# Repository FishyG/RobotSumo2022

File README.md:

# RobotSumo2022

Hello test :)

Hi test. I'm funny.

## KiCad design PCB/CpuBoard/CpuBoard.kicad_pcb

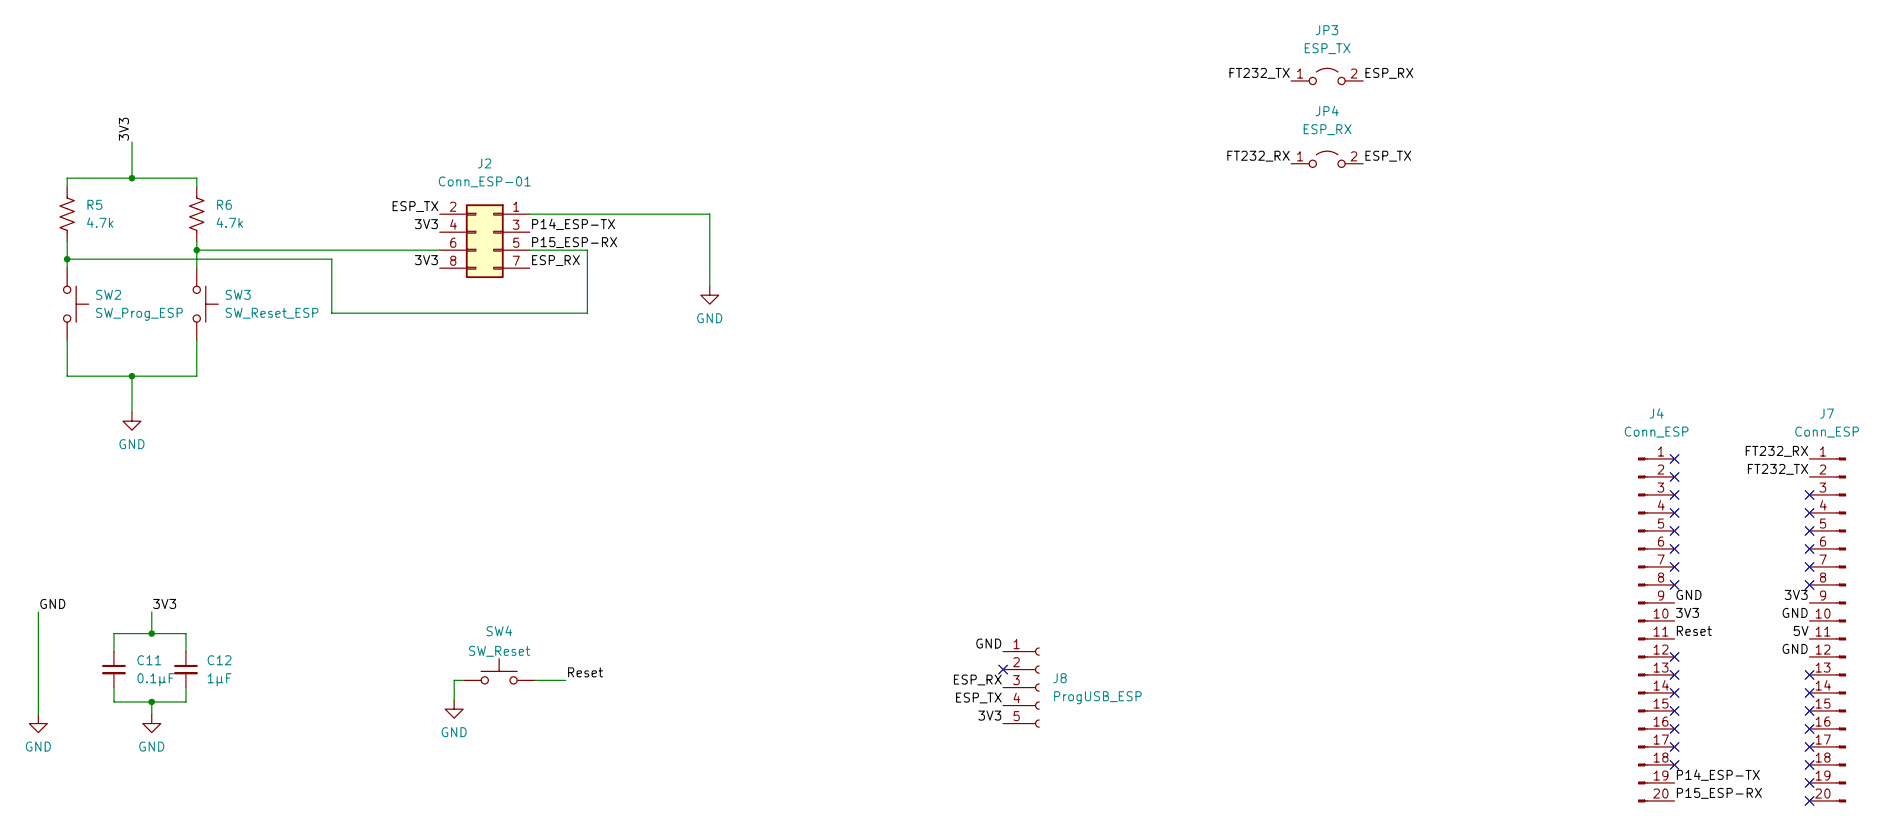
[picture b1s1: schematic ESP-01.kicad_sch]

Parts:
C11: 0.1µF; C_0805_2012Metric_Pad1.18x1.45mm_HandSolder
C12: 1µF; C_0805_2012Metric_Pad1.18x1.45mm_HandSolder
J2: Conn_ESP-01; PinSocket_2x04_P2.54mm_Vertical
J4: Conn_ESP; PinSocket_1x20_P2.54mm_Vertical
J7: Conn_ESP; PinHeader_1x20_P2.54mm_Vertical
J8: ProgUSB_ESP; PinSocket_1x05_P2.54mm_Vertical
JP3: ESP_TX; PinHeader_1x02_P2.54mm_Vertical
JP4: ESP_RX; PinHeader_1x02_P2.54mm_Vertical
R5, R6: 4.7k; R_0805_2012Metric_Pad1.20x1.40mm_HandSolder
SW2: SW_Prog_ESP; SW_SPST_CK_RS282G05A3
SW3: SW_Reset_ESP; SW_SPST_CK_RS282G05A3
SW4: SW_Reset; SW_SPST_CK_RS282G05A3

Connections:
/ESP-01/3V3: C11.1, C12.1, J2.4, J2.8, J4.10, J7.9, J8.5, R5.1, R6.1
/ESP-01/5V: J7.11
/ESP-01/ESP_RX: J2.7, J8.3, JP3.2 (B)
/ESP-01/ESP_TX: J2.2, J8.4, JP4.2 (B)
/ESP-01/FT232_RX: J7.1, JP4.1 (A)
/ESP-01/FT232_TX: J7.2, JP3.1 (A)
/ESP-01/P14_ESP-TX: J2.3, J4.19
/ESP-01/P15_ESP-RX: J2.5, J4.20, R5.2, SW2.1
/ESP-01/Reset: J4.11, SW4.2
GND: C11.2, C12.2, J2.1, J4.9, J7.10, J7.12, J8.1, SW2.2, SW3.2, SW4.1; also elsewhere on the board
unnamed: J2.6, R6.2, SW3.1

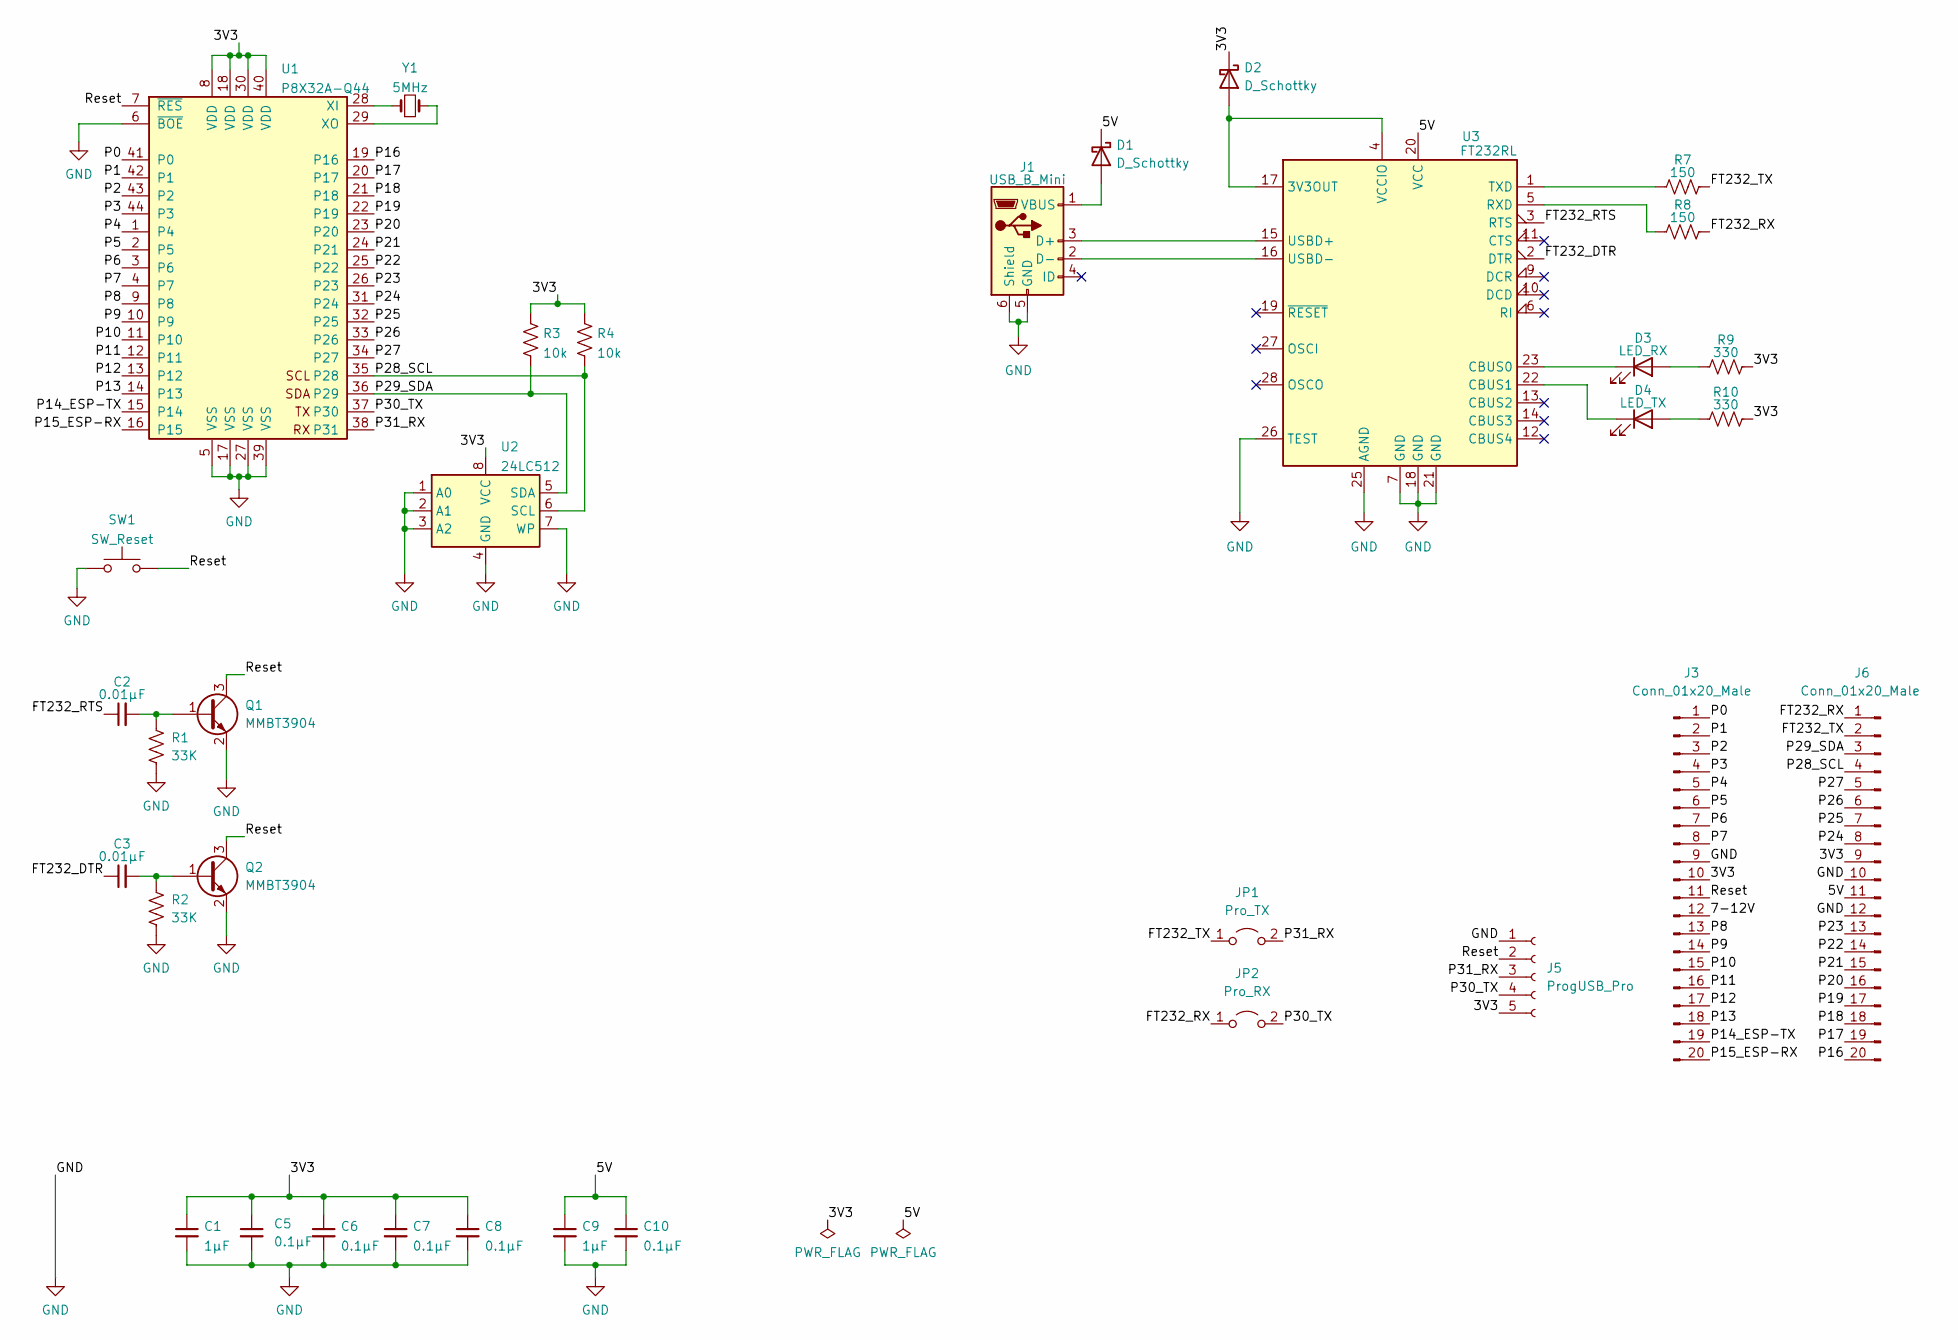
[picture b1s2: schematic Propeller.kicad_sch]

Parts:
C1: 1µF; C_0805_2012Metric_Pad1.18x1.45mm_HandSolder
C2, C3: 0.01µF; C_0805_2012Metric_Pad1.18x1.45mm_HandSolder
C5, C6, C7, C8: 0.1µF; C_0805_2012Metric_Pad1.18x1.45mm_HandSolder
C9: 1µF; C_0603_1608Metric_Pad1.08x0.95mm_HandSolder
C10: 0.1µF; C_0603_1608Metric_Pad1.08x0.95mm_HandSolder
D1, D2: D_Schottky; D_0805_2012Metric_Pad1.15x1.40mm_HandSolder
D3: LED_RX; D_0805_2012Metric_Pad1.15x1.40mm_HandSolder
D4: LED_TX; D_0805_2012Metric_Pad1.15x1.40mm_HandSolder
J1: USB_B_Mini; USB_Mini-B_Wuerth_65100516121_Horizontal
J3, J6: Conn_01x20_Male; PinHeader_1x20_P2.54mm_Vertical
J5: ProgUSB_Pro; PinSocket_1x05_P2.54mm_Horizontal
JP1: Pro_TX; PinHeader_1x02_P2.54mm_Vertical
JP2: Pro_RX; PinHeader_1x02_P2.54mm_Vertical
Q1, Q2: MMBT3904; SOT-23
R1, R2: 33K; R_0805_2012Metric_Pad1.20x1.40mm_HandSolder
R3, R4: 10k; R_0805_2012Metric_Pad1.20x1.40mm_HandSolder
R7, R8: 150; R_0805_2012Metric_Pad1.20x1.40mm_HandSolder
R9, R10: 330; R_0805_2012Metric_Pad1.20x1.40mm_HandSolder
SW1: SW_Reset; SW_SPST_CK_RS282G05A3
U1: P8X32A-Q44; LQFP-44_10x10mm_P0.8mm
U2: 24LC512; SOIC-8-1EP_3.9x4.9mm_P1.27mm_EP2.41x3.81mm
U3: FT232RL; SSOP-28_5.3x10.2mm_P0.65mm
Y1: 5MHz; Crystal_SMD_MicroCrystal_CC1V-T1A-2Pin_8.0x3.7mm_HandSolder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

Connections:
/Propeller/3V3: C1.1, C5.1, C6.1, C7.1, C8.1, D2.1 (K), J3.10, J5.5, J6.9, R3.1, R4.1, R9.2, R10.2, U1.8 (VDD), U1.18 (VDD), U1.30 (VDD), U1.40 (VDD), U2.8 (VCC)
/Propeller/5V: C9.1, C10.1, D1.1 (K), J6.11, U3.20 (VCC)
/Propeller/7-12V: J3.12
/Propeller/FT232_DTR: C3.1, U3.2 (DTR)
/Propeller/FT232_RTS: C2.1, U3.3 (RTS)
/Propeller/FT232_RX: J6.1, JP2.1 (A), R8.2
/Propeller/FT232_TX: J6.2, JP1.1 (A), R7.2
/Propeller/P0: J3.1, U1.41 (P0)
/Propeller/P1: J3.2, U1.42 (P1)
/Propeller/P2: J3.3, U1.43 (P2)
/Propeller/P3: J3.4, U1.44 (P3)
/Propeller/P4: J3.5, U1.1 (P4)
/Propeller/P5: J3.6, U1.2 (P5)
/Propeller/P6: J3.7, U1.3 (P6)
/Propeller/P7: J3.8, U1.4 (P7)
/Propeller/P8: J3.13, U1.9 (P8)
/Propeller/P9: J3.14, U1.10 (P9)
/Propeller/P10: J3.15, U1.11 (P10)
/Propeller/P11: J3.16, U1.12 (P11)
/Propeller/P12: J3.17, U1.13 (P12)
/Propeller/P13: J3.18, U1.14 (P13)
/Propeller/P14_ESP-TX: J3.19, U1.15 (P14)
/Propeller/P15_ESP-RX: J3.20, U1.16 (P15)
/Propeller/P16: J6.20, U1.19 (P16)
/Propeller/P17: J6.19, U1.20 (P17)
/Propeller/P18: J6.18, U1.21 (P18)
/Propeller/P19: J6.17, U1.22 (P19)
/Propeller/P20: J6.16, U1.23 (P20)
/Propeller/P21: J6.15, U1.24 (P21)
/Propeller/P22: J6.14, U1.25 (P22)
/Propeller/P23: J6.13, U1.26 (P23)
/Propeller/P24: J6.8, U1.31 (P24)
/Propeller/P25: J6.7, U1.32 (P25)
/Propeller/P26: J6.6, U1.33 (P26)
/Propeller/P27: J6.5, U1.34 (P27)
/Propeller/P28_SCL: J6.4, R4.2, U1.35 (P28), U2.6 (SCL)
/Propeller/P29_SDA: J6.3, R3.2, U1.36 (P29), U2.5 (SDA)
/Propeller/P30_TX: J5.4, JP2.2 (B), U1.37 (P30)
/Propeller/P31_RX: J5.3, JP1.2 (B), U1.38 (P31)
/Propeller/Reset: J3.11, J5.2, Q1.3 (C), Q2.3 (C), SW1.2, U1.7 (~RES)
GND: C1.2, C5.2, C6.2, C7.2, C8.2, C9.2, C10.2, J1.5 (GND), J1.6 (Shield), J3.9, J5.1, J6.10, J6.12, Q1.2 (E), Q2.2 (E), R1.2, R2.2, SW1.1, U1.5 (VSS), U1.6 (~BOE), U1.17 (VSS), U1.27 (VSS), U1.39 (VSS), U2.1 (A0), U2.2 (A1), U2.3 (A2), U2.4 (GND), U2.7 (WP), U3.7 (GND), U3.18 (GND), U3.21 (GND), U3.25 (AGND), U3.26 (TEST); also elsewhere on the board
unnamed: C2.2, Q1.1 (B), R1.1
unnamed: C3.2, Q2.1 (B), R2.1
unnamed: D1.2 (A), J1.1 (VBUS)
unnamed: D2.2 (A), U3.4 (VCCIO), U3.17 (3V3OUT)
unnamed: D3.1 (K), U3.23 (CBUS0)
unnamed: D3.2 (A), R9.1
unnamed: D4.1 (K), U3.22 (CBUS1)
unnamed: D4.2 (A), R10.1
unnamed: J1.2 (D-), U3.16 (USBD-)
unnamed: J1.3 (D+), U3.15 (USBD+)
unnamed: R7.1, U3.1 (TXD)
unnamed: R8.1, U3.5 (RXD)
unnamed: U1.28 (XI), Y1.1
unnamed: U1.29 (XO), Y1.2

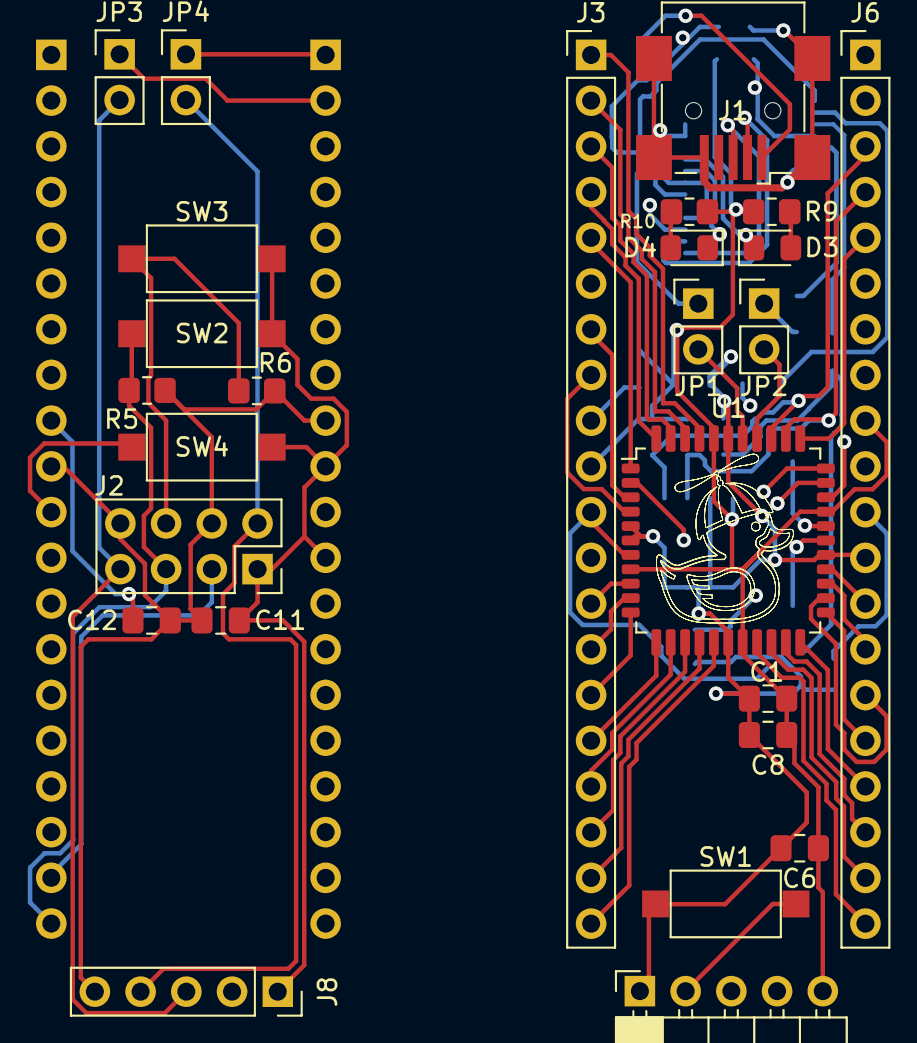
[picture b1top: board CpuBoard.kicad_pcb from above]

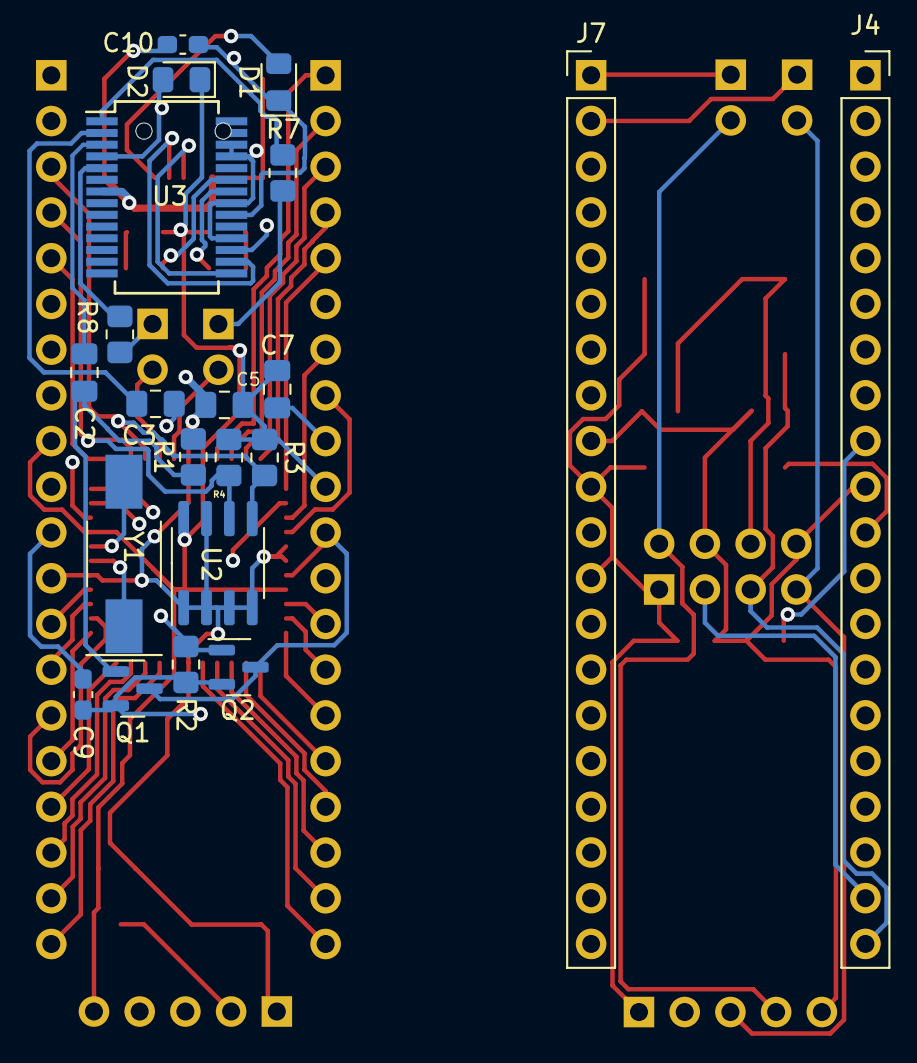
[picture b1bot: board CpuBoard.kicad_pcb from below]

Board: 4 copper layers, 47 parts (21 on the bottom side), 63 nets.

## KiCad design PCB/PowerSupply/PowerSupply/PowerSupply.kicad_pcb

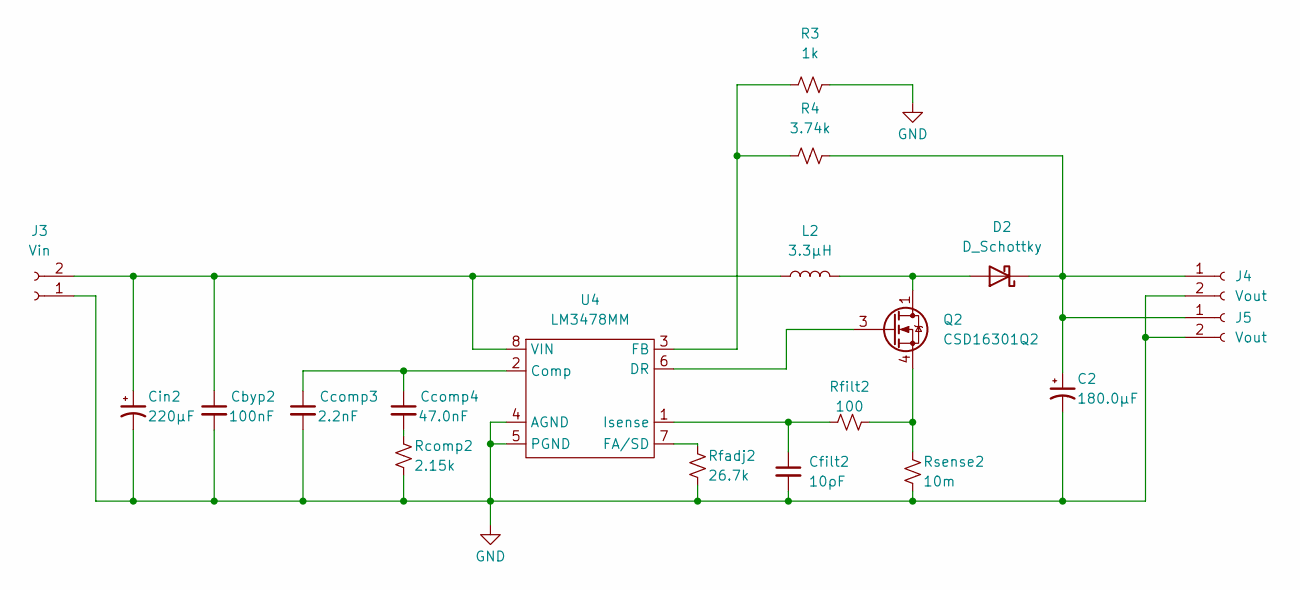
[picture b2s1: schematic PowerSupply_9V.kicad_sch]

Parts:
C2: 180.0μF; CP_Elec_10x10
Cbyp2: 100nF; C_0805_2012Metric_Pad1.18x1.45mm_HandSolder
Ccomp3: 2.2nF; C_0805_2012Metric_Pad1.18x1.45mm_HandSolder
Ccomp4: 47.0nF; R_0805_2012Metric_Pad1.20x1.40mm_HandSolder
Cfilt2: 10ρF; C_0805_2012Metric_Pad1.18x1.45mm_HandSolder
Cin2: 220µF; C_0805_2012Metric_Pad1.18x1.45mm_HandSolder
D2: D_Schottky; D_SMB-SMC_Universal_Handsoldering
J3: Vin; PinHeader_1x02_P2.54mm_Vertical
J4, J5: Vout; PinHeader_1x02_P2.54mm_Vertical
L2: 3.3µH; L_TDK_VLP8040
Q2: CSD16301Q2; Texas_DQK
R3: 1k; R_0805_2012Metric_Pad1.20x1.40mm_HandSolder
R4: 3.74k; R_0805_2012Metric_Pad1.20x1.40mm_HandSolder
Rcomp2: 2.15k; R_0805_2012Metric_Pad1.20x1.40mm_HandSolder
Rfadj2: 26.7k; R_0805_2012Metric_Pad1.20x1.40mm_HandSolder
Rfilt2: 100; R_0805_2012Metric_Pad1.20x1.40mm_HandSolder
Rsense2: 10m; R_1206_3216Metric_Pad1.30x1.75mm_HandSolder
U4: LM3478MM; SOIC-8-1EP_3.9x4.9mm_P1.27mm_EP2.29x3mm

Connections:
GND: C2.2, Cbyp2.2, Ccomp3.2, Cfilt2.2, Cin2.2, J3.1, J4.2, J5.2, R3.2, Rcomp2.2, Rfadj2.2, Rsense2.2, U4.4 (AGND), U4.5 (PGND); also elsewhere on the board
unnamed: C2.1, D2.1 (K), J4.1, J5.1, R4.2
unnamed: Cbyp2.1, Cin2.1, J3.2, L2.1, U4.8 (VIN)
unnamed: Ccomp3.1, Ccomp4.1, U4.2 (Comp)
unnamed: Ccomp4.2, Rcomp2.1
unnamed: Cfilt2.1, Rfilt2.1, U4.1 (Isense)
unnamed: D2.2 (A), L2.2, Q2.1 (D), Q2.2 (D), Q2.5 (D), Q2.6 (D), Q2.8 (D)
unnamed: Q2.3 (G), U4.6 (DR)
unnamed: Q2.4 (S), Q2.7 (S), Rfilt2.2, Rsense2.1
unnamed: R3.1, R4.1, U4.3 (FB)
unnamed: Rfadj2.1, U4.7 (FA/SD)

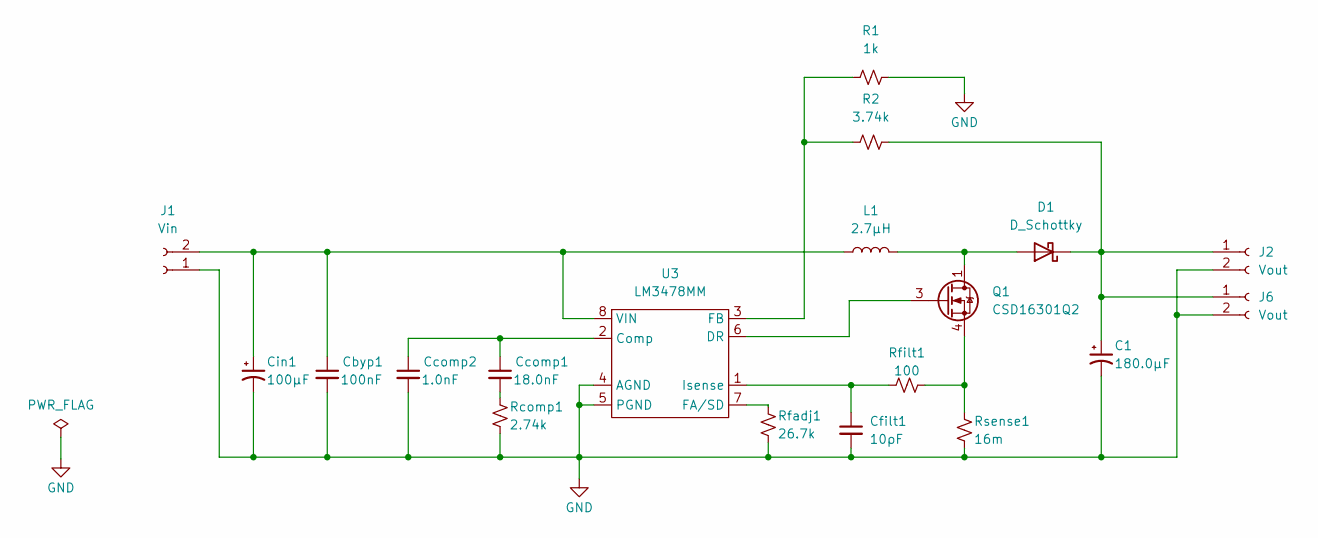
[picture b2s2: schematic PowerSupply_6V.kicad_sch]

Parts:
C1: 180.0μF; CP_Elec_10x10
Cbyp1: 100nF; C_0805_2012Metric_Pad1.18x1.45mm_HandSolder
Ccomp1: 18.0nF; R_0805_2012Metric_Pad1.20x1.40mm_HandSolder
Ccomp2: 1.0nF; C_0805_2012Metric_Pad1.18x1.45mm_HandSolder
Cfilt1: 10ρF; C_0805_2012Metric_Pad1.18x1.45mm_HandSolder
Cin1: 100µF; C_0805_2012Metric_Pad1.18x1.45mm_HandSolder
D1: D_Schottky; D_SMB-SMC_Universal_Handsoldering
J1: Vin; PinHeader_1x02_P2.54mm_Vertical
J2, J6: Vout; PinHeader_1x02_P2.54mm_Vertical
L1: 2.7µH; L_TDK_VLP8040
Q1: CSD16301Q2; Texas_DQK
R1: 1k; R_0805_2012Metric_Pad1.20x1.40mm_HandSolder
R2: 3.74k; R_0805_2012Metric_Pad1.20x1.40mm_HandSolder
Rcomp1: 2.74k; R_0805_2012Metric_Pad1.20x1.40mm_HandSolder
Rfadj1: 26.7k; R_0805_2012Metric_Pad1.20x1.40mm_HandSolder
Rfilt1: 100; R_0805_2012Metric_Pad1.20x1.40mm_HandSolder
Rsense1: 16m; R_1206_3216Metric_Pad1.30x1.75mm_HandSolder
U3: LM3478MM; SOIC-8-1EP_3.9x4.9mm_P1.27mm_EP2.29x3mm

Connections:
GND: C1.2, Cbyp1.2, Ccomp2.2, Cfilt1.2, Cin1.2, J1.1, J2.2, J6.2, R1.2, Rcomp1.2, Rfadj1.2, Rsense1.2, U3.4 (AGND), U3.5 (PGND); also elsewhere on the board
unnamed: C1.1, D1.1 (K), J2.1, J6.1, R2.2
unnamed: Cbyp1.1, Cin1.1, J1.2, L1.1, U3.8 (VIN)
unnamed: Ccomp1.1, Ccomp2.1, U3.2 (Comp)
unnamed: Ccomp1.2, Rcomp1.1
unnamed: Cfilt1.1, Rfilt1.1, U3.1 (Isense)
unnamed: D1.2 (A), L1.2, Q1.1 (D), Q1.2 (D), Q1.5 (D), Q1.6 (D), Q1.8 (D)
unnamed: Q1.3 (G), U3.6 (DR)
unnamed: Q1.4 (S), Q1.7 (S), Rfilt1.2, Rsense1.1
unnamed: R1.1, R2.1, U3.3 (FB)
unnamed: Rfadj1.1, U3.7 (FA/SD)

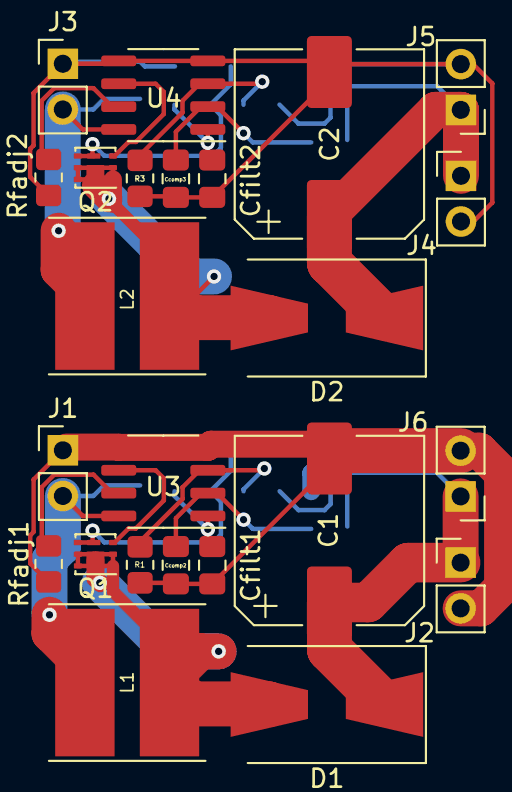
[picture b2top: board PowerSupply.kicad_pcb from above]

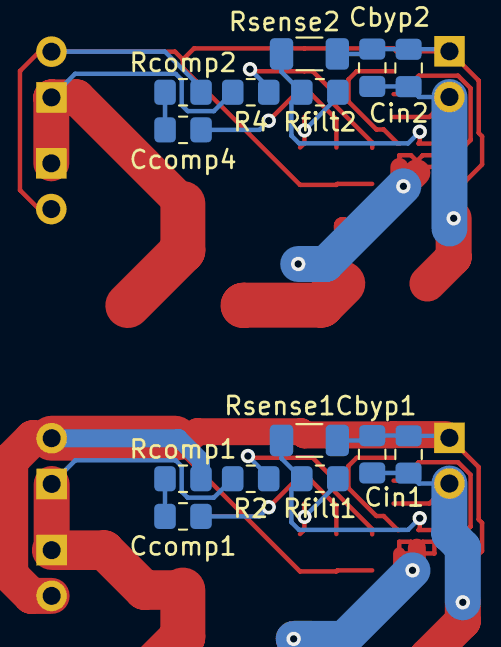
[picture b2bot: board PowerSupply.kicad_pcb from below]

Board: 2 copper layers, 38 parts (14 on the bottom side), 21 nets.

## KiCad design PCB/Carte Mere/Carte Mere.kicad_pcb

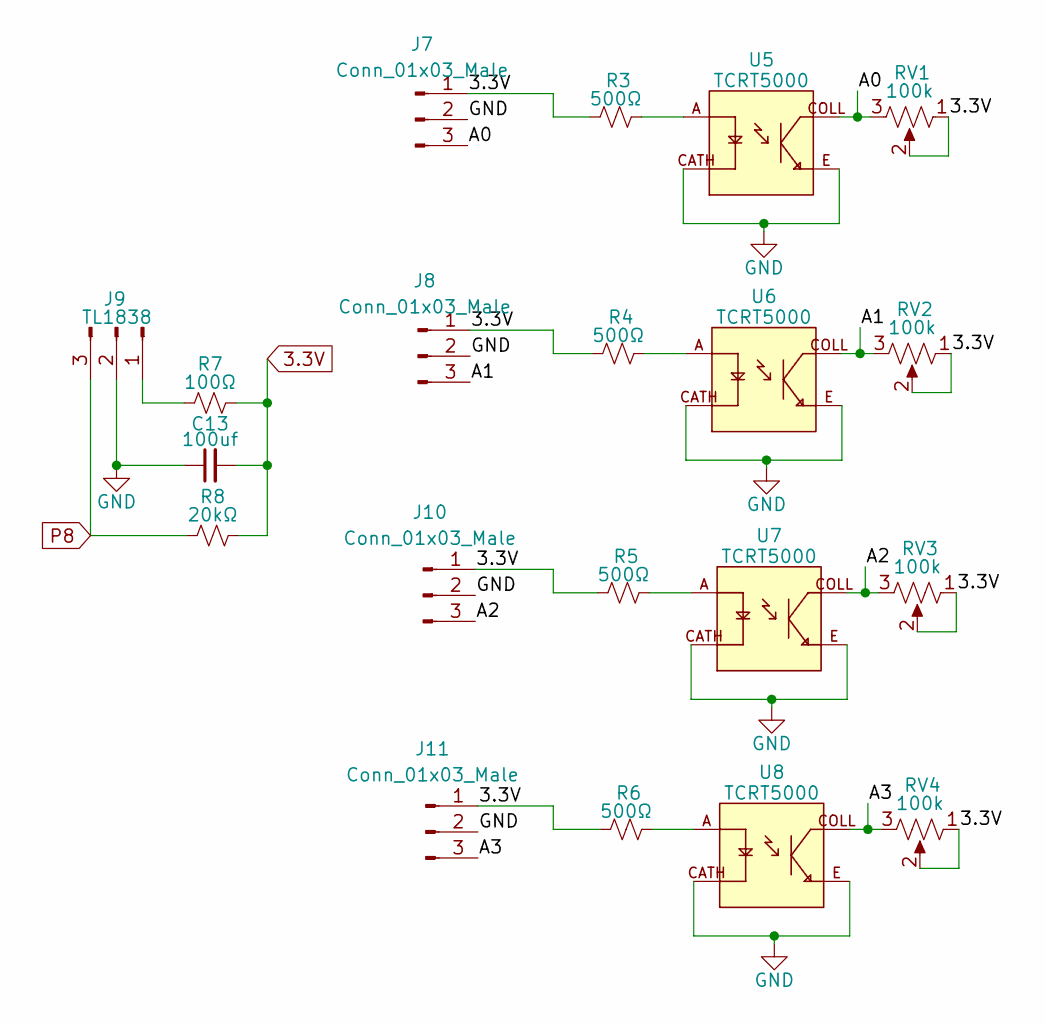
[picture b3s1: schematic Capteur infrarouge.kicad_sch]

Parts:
C13: 100uf; C_0805_2012Metric_Pad1.18x1.45mm_HandSolder
J7, J8, J10, J11: Conn_01x03_Male; PinHeader_1x03_P2.54mm_Vertical
J9: TL1838; PinHeader_1x03_P2.54mm_Vertical
R3, R4, R5, R6: 500Ω; R_0805_2012Metric_Pad1.20x1.40mm_HandSolder
R7: 100Ω; R_0805_2012Metric_Pad1.20x1.40mm_HandSolder
R8: 20kΩ; R_0805_2012Metric_Pad1.20x1.40mm_HandSolder
RV1, RV2, RV3, RV4: 100k; Potentiometer_ACP_CA6-H2,5_Horizontal
U5, U6, U7, U8: TCRT5000; OPTO_TCRT5000; PARTREV 1.7

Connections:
3.3V: C13.2, J7.1, J8.1, J10.1, J11.1, R3.1, R4.1, R5.1, R6.1, R7.2, R8.2, RV1.1, RV1.2, RV2.1, RV2.2, RV3.1, RV3.2, RV4.1, RV4.2; also elsewhere on the board
/Capteur/A0: J7.3, RV1.3, U5.COLL
/Capteur/A1: J8.3, RV2.3, U6.COLL
/Capteur/A2: J10.3, RV3.3, U7.COLL
/Capteur/A3: J11.3, RV4.3, U8.COLL
GND: C13.1, J7.2, J8.2, J9.2, J10.2, J11.2, U5.CATH, U5.E, U6.CATH, U6.E, U7.CATH, U7.E, U8.CATH, U8.E; also elsewhere on the board
unnamed: J9.1, R7.1
unnamed: R3.2, U5.A
unnamed: R4.2, U6.A
unnamed: R5.2, U7.A
unnamed: R6.2, U8.A
P8: J9.3, R8.1; also elsewhere on the board

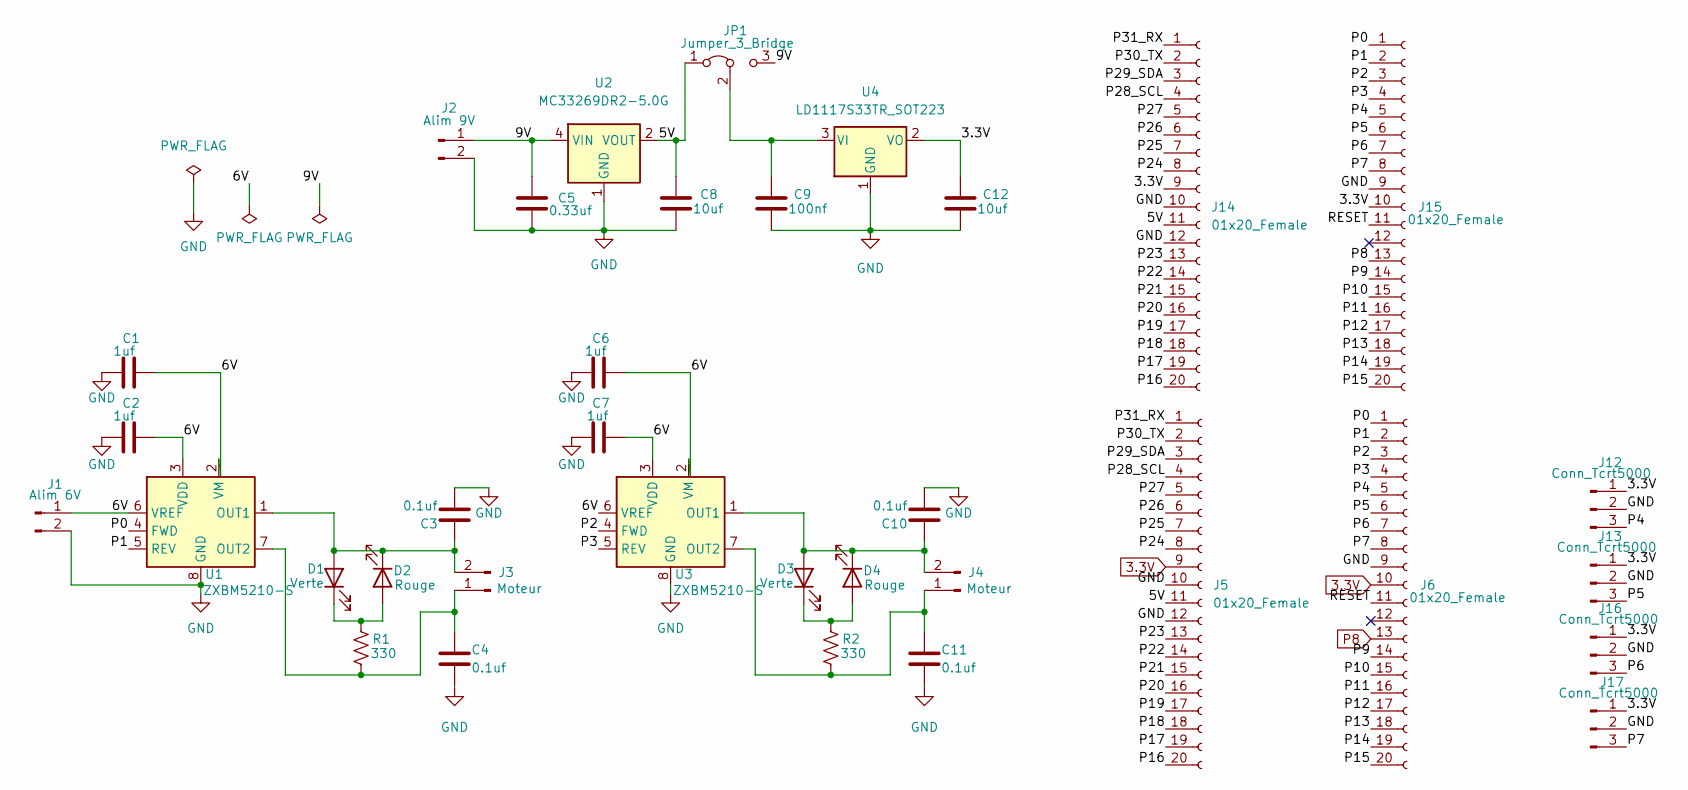
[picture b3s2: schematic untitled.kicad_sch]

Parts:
C1, C2, C6, C7: 1uf; C_0805_2012Metric_Pad1.18x1.45mm_HandSolder
C3, C4, C10, C11: 0.1uf; C_0805_2012Metric_Pad1.18x1.45mm_HandSolder
C5: 0.33uf; C_0805_2012Metric_Pad1.18x1.45mm_HandSolder
C8, C12: 10uf; C_0805_2012Metric_Pad1.18x1.45mm_HandSolder
C9: 100nf; C_0805_2012Metric_Pad1.18x1.45mm_HandSolder
D1, D3: Verte; D_0805_2012Metric_Pad1.15x1.40mm_HandSolder
D2, D4: Rouge; D_0805_2012Metric_Pad1.15x1.40mm_HandSolder
J1: Alim 6V; PinHeader_1x02_P2.54mm_Vertical
J2: Alim 9V; PinHeader_1x02_P2.54mm_Vertical
J3, J4: Moteur; PinHeader_1x02_P2.54mm_Vertical
J5, J6, J14, J15: 01x20_Female; PinSocket_1x20_P2.54mm_Vertical
J12, J13, J16, J17: Conn_Tcrt5000; PinHeader_1x03_P2.54mm_Vertical
JP1: Jumper_3_Bridge; PinHeader_1x03_P2.54mm_Vertical
R1, R2: 330; R_0805_2012Metric_Pad1.20x1.40mm_HandSolder
U1, U3: ZXBM5210-S; SOIC-8_3.9x4.9mm_P1.27mm
U2: MC33269DR2-5.0G; SOIC-8_3.9x4.9mm_P1.27mm
U4: LD1117S33TR_SOT223; TO-252-2

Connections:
3.3V: C12.1, J5.9, J6.10, J12.1, J13.1, J14.9, J15.10, J16.1, J17.1, U4.2 (VO); also elsewhere on the board
/Carte Mere/5V: C8.1, J5.11, J14.11, JP1.1 (A), U2.2 (VOUT), U2.3 (VOUT), U2.6 (VOUT), U2.7 (VOUT)
/Carte Mere/6V: C1.1, C2.1, C6.1, C7.1, J1.1, U1.2 (VM), U1.3 (VDD), U1.6 (VREF), U3.2 (VM), U3.3 (VDD), U3.6 (VREF)
/Carte Mere/9V: C5.1, J2.1, JP1.3 (B), U2.4 (VIN)
/Carte Mere/P0: J6.1, J15.1, U1.4 (FWD)
/Carte Mere/P1: J6.2, J15.2, U1.5 (REV)
/Carte Mere/P2: J6.3, J15.3, U3.4 (FWD)
/Carte Mere/P3: J6.4, J15.4, U3.5 (REV)
/Carte Mere/P4: J6.5, J12.3, J15.5
/Carte Mere/P5: J6.6, J13.3, J15.6
/Carte Mere/P6: J6.7, J15.7, J16.3
/Carte Mere/P7: J6.8, J15.8, J17.3
/Carte Mere/P9: J6.14, J15.14
/Carte Mere/P10: J6.15, J15.15
/Carte Mere/P11: J6.16, J15.16
/Carte Mere/P12: J6.17, J15.17
/Carte Mere/P13: J6.18, J15.18
/Carte Mere/P14: J6.19, J15.19
/Carte Mere/P15: J6.20, J15.20
/Carte Mere/P16: J5.20, J14.20
/Carte Mere/P17: J5.19, J14.19
/Carte Mere/P18: J5.18, J14.18
/Carte Mere/P19: J5.17, J14.17
/Carte Mere/P20: J5.16, J14.16
/Carte Mere/P21: J5.15, J14.15
/Carte Mere/P22: J5.14, J14.14
/Carte Mere/P23: J5.13, J14.13
/Carte Mere/P24: J5.8, J14.8
/Carte Mere/P25: J5.7, J14.7
/Carte Mere/P26: J5.6, J14.6
/Carte Mere/P27: J5.5, J14.5
/Carte Mere/P28_SCL: J5.4, J14.4
/Carte Mere/P29_SDA: J5.3, J14.3
/Carte Mere/P30_TX: J5.2, J14.2
/Carte Mere/P31_RX: J5.1, J14.1
/Carte Mere/RESET: J6.11, J15.11
GND: C1.2, C2.2, C3.2, C4.2, C5.2, C6.2, C7.2, C8.2, C9.2, C10.2, C11.2, C12.2, J1.2, J2.2, J5.10, J5.12, J6.9, J12.2, J13.2, J14.10, J14.12, J15.9, J16.2, J17.2, U1.8 (GND), U2.1 (GND), U3.8 (GND), U4.1 (GND); also elsewhere on the board
unnamed: C3.1, D1.2 (A), D2.1 (K), J3.2, U1.1 (OUT1)
unnamed: C4.1, J3.1, R1.1, U1.7 (OUT2)
unnamed: C9.1, JP1.2 (C), U4.3 (VI)
unnamed: C10.1, D3.2 (A), D4.1 (K), J4.2, U3.1 (OUT1)
unnamed: C11.1, J4.1, R2.1, U3.7 (OUT2)
unnamed: D1.1 (K), D2.2 (A), R1.2
unnamed: D3.1 (K), D4.2 (A), R2.2
P8: J6.13, J15.13; also elsewhere on the board

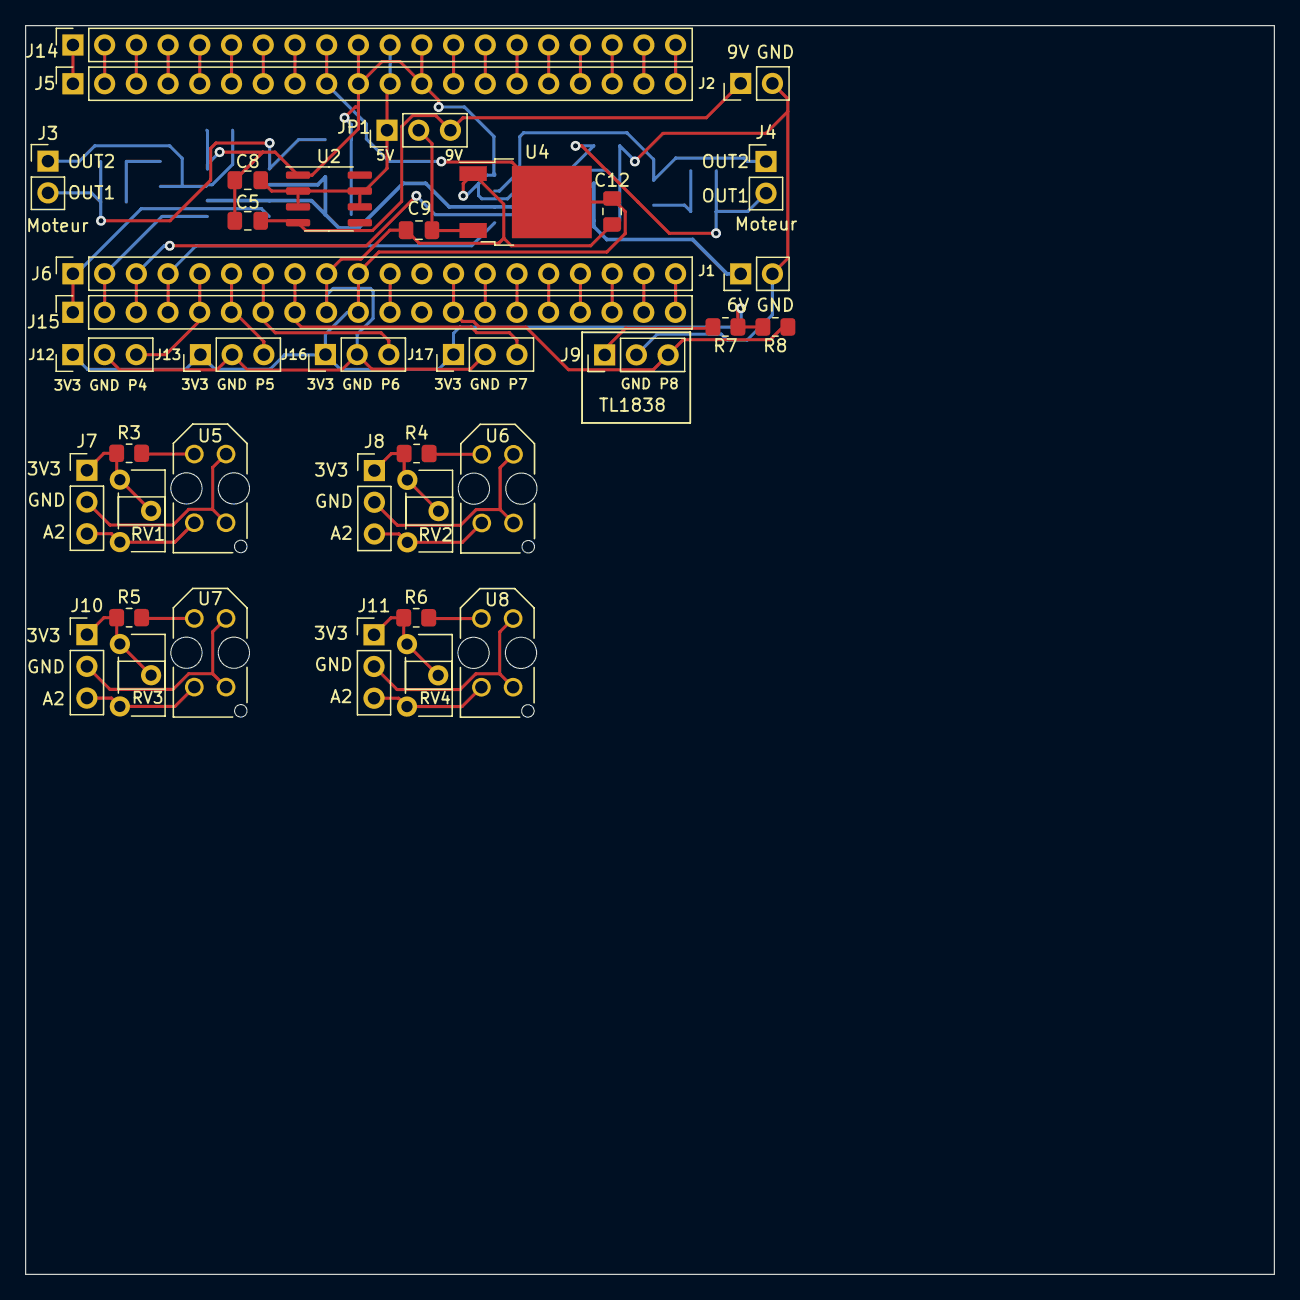
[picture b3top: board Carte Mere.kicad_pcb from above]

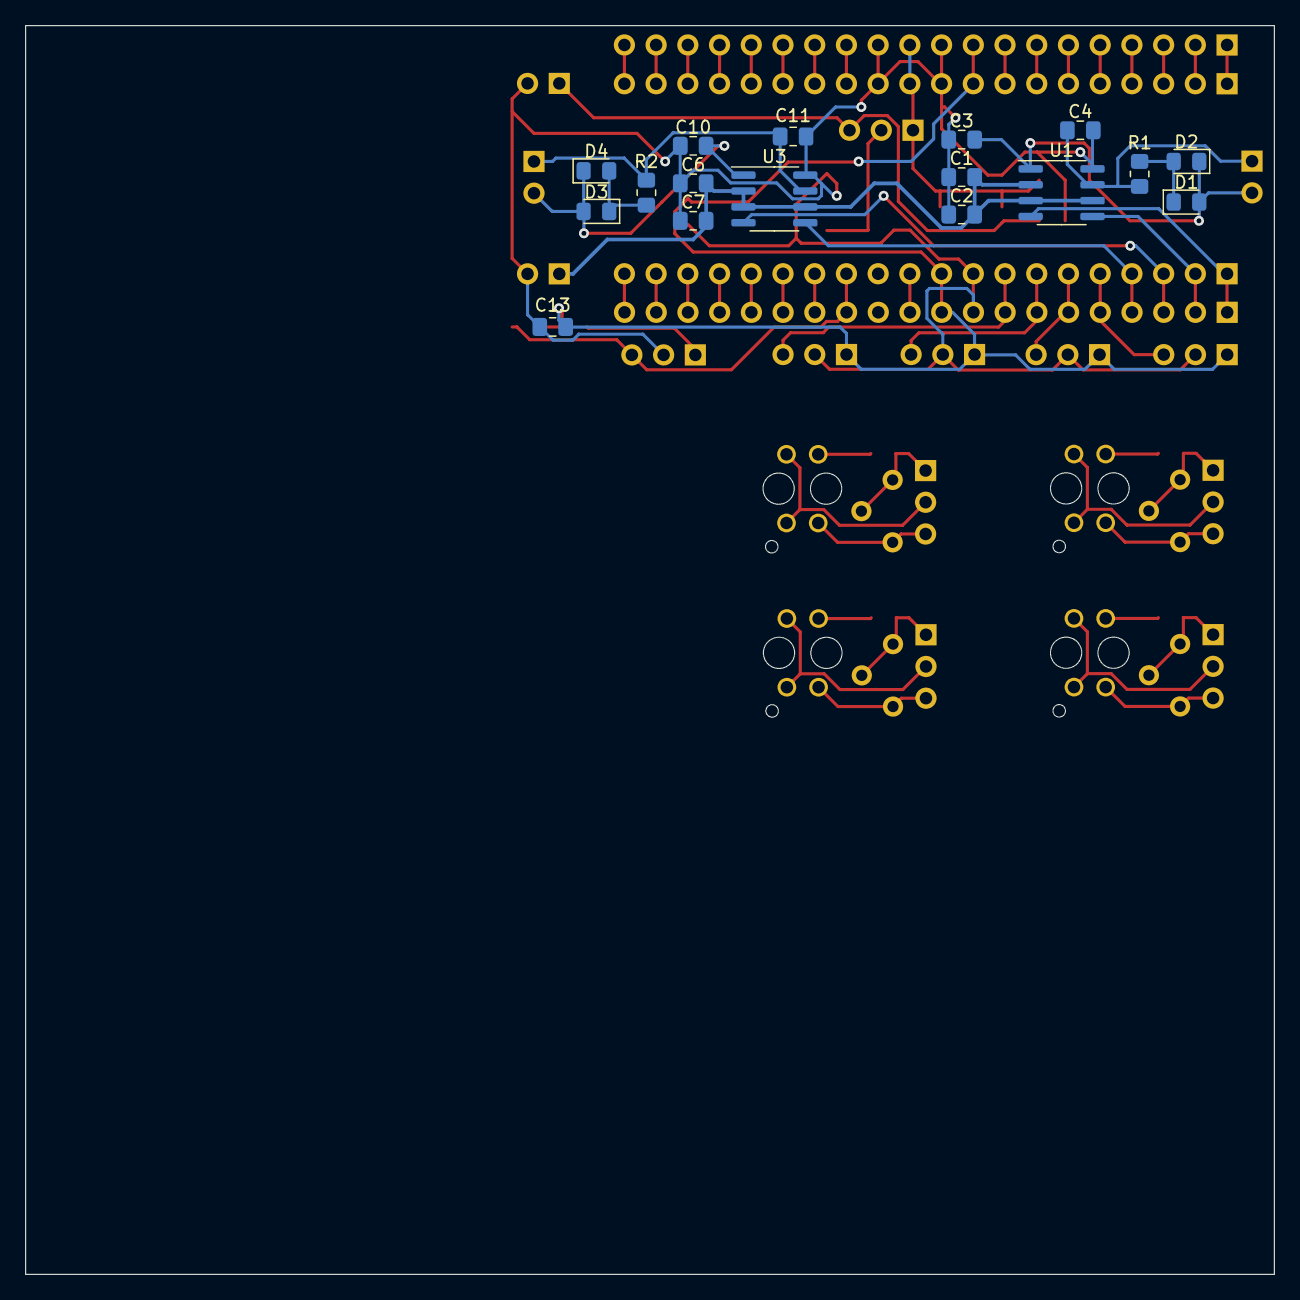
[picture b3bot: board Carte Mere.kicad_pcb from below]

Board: 4 copper layers, 100.0 x 100.0 mm, 55 parts (17 on the bottom side), 54 nets.
